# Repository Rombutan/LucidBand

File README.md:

# LucidBand! - The really thin, no-charge smartwatch.
## Philosophy
I quite like the idea of having lots of easily accessible data about myself. Fitness and biological data can be a big help in organizing and optimizing one's life, and I think everyone should have access to that data about *themselves*. 
I want something really thin and somewhat modular that can collect a lot of the data I want to have access to.

## Technology
LucidBand hasa flexible solar cell and everything but the display in the wristband!
The only thing in the face is the display - everything else is on a pcb built into the bottom of the wristband (under your wrist). This lets the face be really thin - hopefully around 7mm - and also allows operation without the display (think: ankle band).
The band will be cast out of a semi-flexible clear epoxy or something.

## Chips
* MCU:			ESP32-C3-WROOM-02-N4
* ENERGY:	  BQ25504
* GYRO:		  BMI270
* SOLAR:		ONP2.4-15X94
<br>
BOM cost for 5 boards with shipping to California turned up to be around 150$. I'm guessing parts for only 1 board would be around 100$ with shipping.

## Screenshots

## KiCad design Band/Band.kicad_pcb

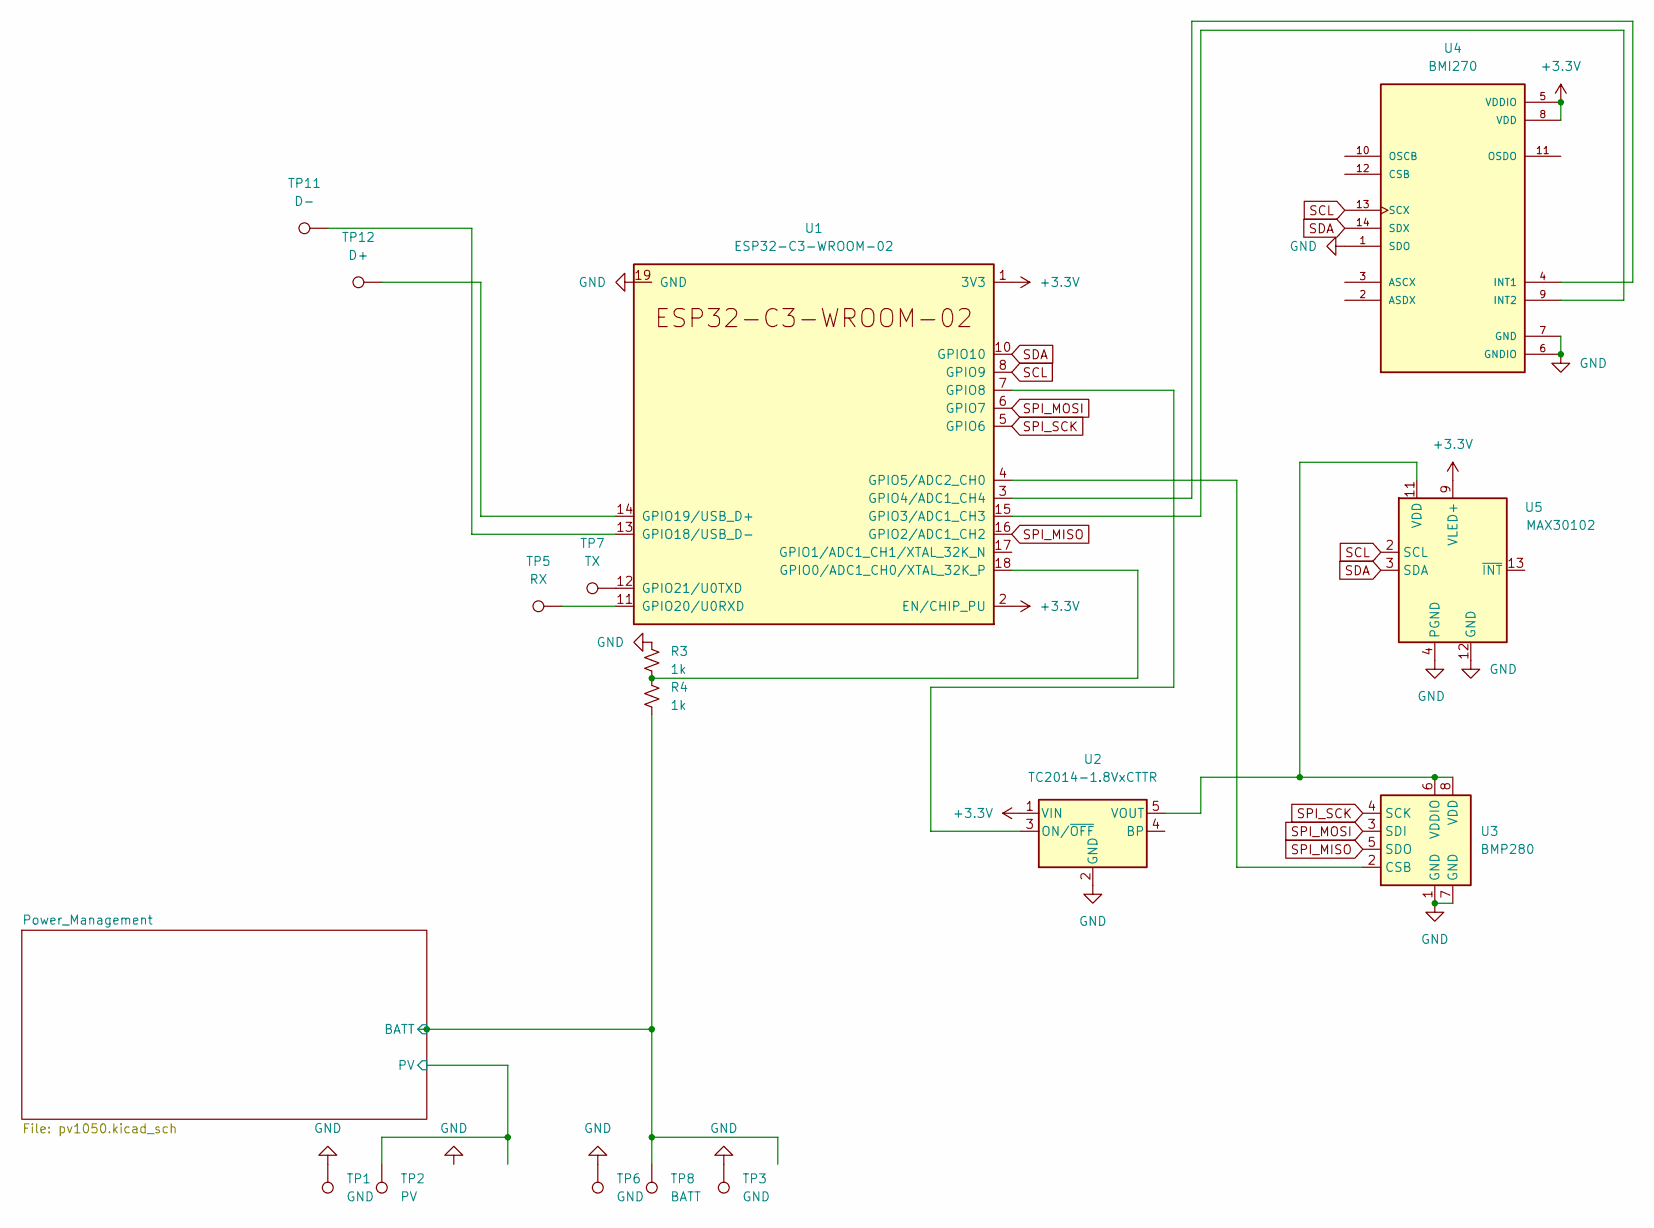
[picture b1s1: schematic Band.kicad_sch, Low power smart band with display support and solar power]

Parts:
R3, R4: 1k; R_0402_1005Metric
TP1, TP3, TP6: GND; TestPoint_Pad_2.0x2.0mm
TP2: PV; TestPoint_Pad_2.0x2.0mm
TP5: RX; TestPoint_Pad_2.0x2.0mm
TP7: TX; TestPoint_Pad_2.0x2.0mm
TP8: BATT; TestPoint_Pad_2.0x2.0mm
TP11: D-; TestPoint_Pad_2.0x2.0mm
TP12: D+; TestPoint_Pad_2.0x2.0mm
U1: ESP32-C3-WROOM-02
U2: TC2014-1.8VxCTTR; SOT-23-5
U3: BMP280; Bosch_LGA-8_2x2.5mm_P0.65mm_ClockwisePinNumbering
U4: BMI270; XDCR_BMI270
U5: MAX30102; Maxim_OLGA-14_3.3x5.6mm_P0.8mm

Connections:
+3.3V: U1.1 (3V3), U1.2 (EN/CHIP_PU), U2.1 (VIN), U4.5 (VDDIO), U4.8 (VDD), U5.9 (VLED+), U5.10 (VLED+); also elsewhere on the board
/Power_Management/BATT: R4.2, TP8.1; also elsewhere on the board
/Power_Management/PV: TP2.1; also elsewhere on the board
GND: R3.1, TP1.1, TP3.1, TP6.1, U1.9 (GND), U1.19 (GND), U2.2 (GND), U3.1 (GND), U3.7 (GND), U4.1 (SDO), U4.6 (GNDIO), U4.7 (GND), U5.4 (PGND), U5.12 (GND); also elsewhere on the board
unnamed: R3.2, R4.1, U1.18 (GPIO0/ADC1_CH0/XTAL_32K_P)
unnamed: TP5.1, U1.11 (GPIO20/U0RXD)
unnamed: TP7.1, U1.12 (GPIO21/U0TXD)
unnamed: U1.3 (GPIO4/ADC1_CH4), U4.4 (INT1)
unnamed: U1.4 (GPIO5/ADC2_CH0), U3.2 (CSB)
unnamed: U1.7 (GPIO8), U2.3 (ON/~OFF)
unnamed: TP11.1, U1.13 (GPIO18/USB_D-)
unnamed: TP12.1, U1.14 (GPIO19/USB_D+)
unnamed: U1.15 (GPIO3/ADC1_CH3), U4.9 (INT2)
unnamed: U2.5 (VOUT), U3.6 (VDDIO), U3.8 (VDD), U5.11 (VDD)
SCL: U1.8 (GPIO9), U4.13 (SCX), U5.2 (SCL)
SDA: U1.10 (GPIO10), U4.14 (SDX), U5.3 (SDA)
SPI_MISO: U1.16 (GPIO2/ADC1_CH2), U3.5 (SDO)
SPI_MOSI: U1.6 (GPIO7), U3.3 (SDI)
SPI_SCK: U1.5 (GPIO6), U3.4 (SCK)

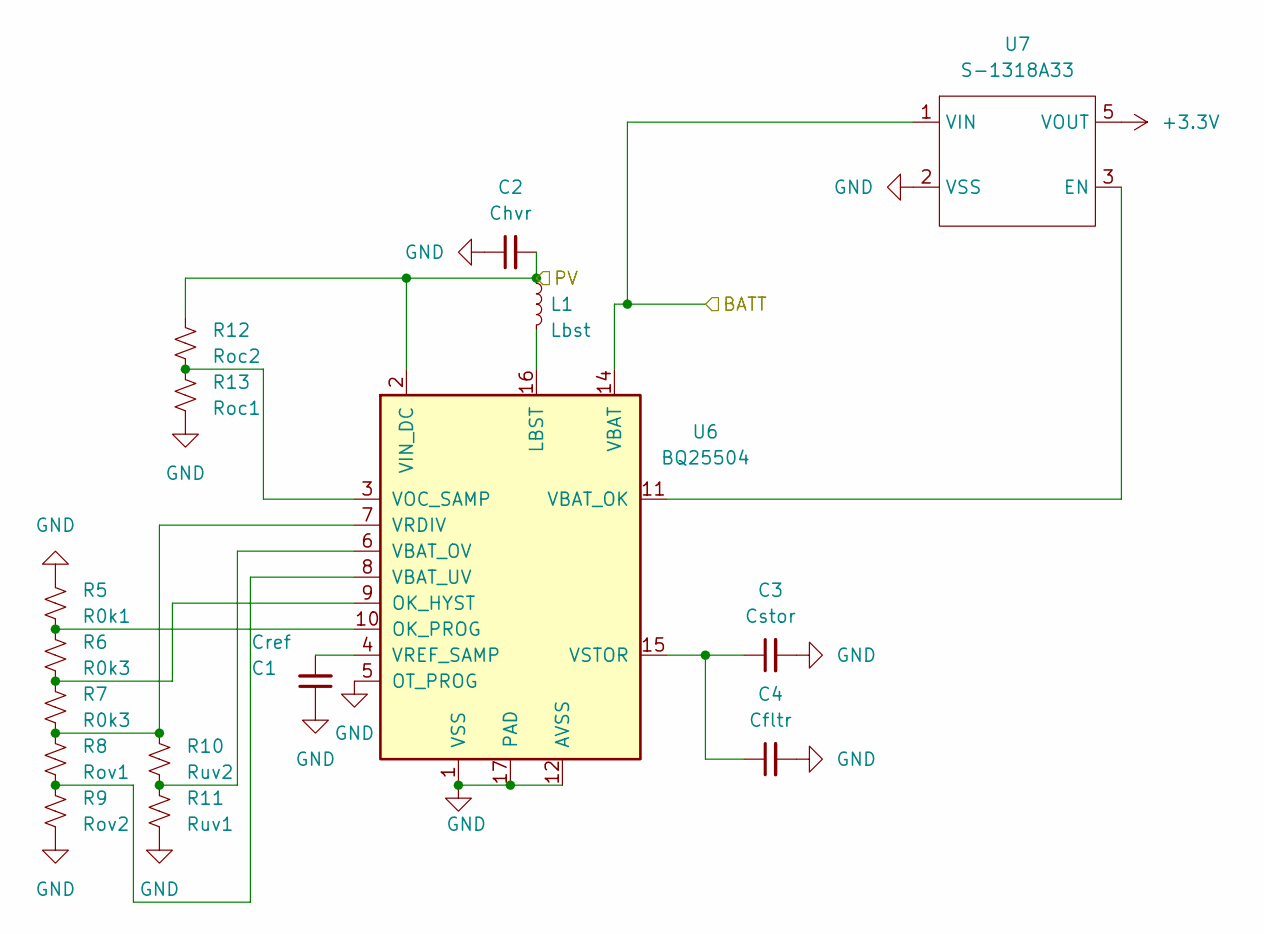
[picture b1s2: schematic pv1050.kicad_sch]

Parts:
C1: Cref; C_0402_1005Metric
C2: Chvr; C_0402_1005Metric
C3: Cstor; C_0805_2012Metric
C4: Cfltr; C_0402_1005Metric
L1: Lbst; L_1210_3225Metric
R5: R0k1; R_0402_1005Metric
R6, R7: R0k3; R_0402_1005Metric
R8: Rov1; R_0402_1005Metric
R9: Rov2; R_0402_1005Metric
R10: Ruv2; R_0402_1005Metric
R11: Ruv1; R_0402_1005Metric
R12: Roc2; R_0402_1005Metric
R13: Roc1; R_0402_1005Metric
U6: BQ25504; VQFN-16-1EP_3x3mm_P0.5mm_EP1.8x1.8mm
U7: S-1318A33; SOT-23-5

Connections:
+3.3V: U7.5 (VOUT); also elsewhere on the board
/Power_Management/BATT: U6.14 (VBAT), U7.1 (VIN); also elsewhere on the board
/Power_Management/PV: C2.2, L1.1, R12.1, U6.2 (VIN_DC); also elsewhere on the board
GND: C1.1, C2.1, C3.2, C4.2, R5.1, R9.2, R11.2, R13.2, U6.1 (VSS), U6.5 (OT_PROG), U6.12 (AVSS), U6.13 (VSS), U6.17 (PAD), U7.2 (VSS); also elsewhere on the board
unnamed: C1.2, U6.4 (VREF_SAMP)
unnamed: C3.1, C4.1, U6.15 (VSTOR)
unnamed: L1.2, U6.16 (LBST)
unnamed: R5.2, R6.1, U6.10 (OK_PROG)
unnamed: R6.2, R7.1, U6.9 (OK_HYST)
unnamed: R8.2, R9.1, U6.8 (VBAT_UV)
unnamed: R7.2, R8.1, R10.1, U6.7 (VRDIV)
unnamed: R10.2, R11.1, U6.6 (VBAT_OV)
unnamed: R12.2, R13.1, U6.3 (VOC_SAMP)
unnamed: U6.11 (VBAT_OK), U7.3 (EN)

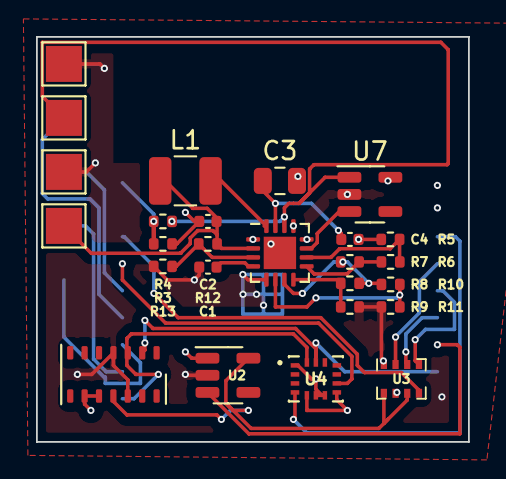
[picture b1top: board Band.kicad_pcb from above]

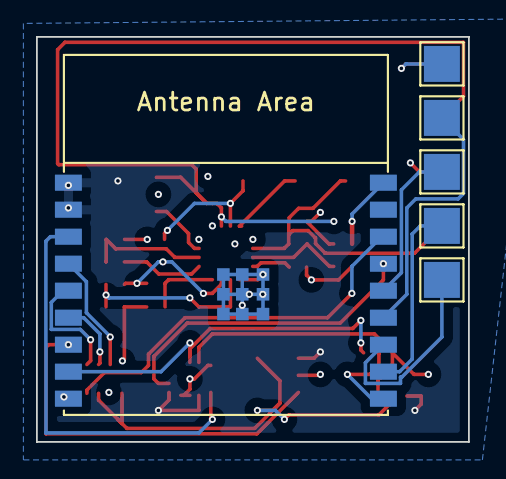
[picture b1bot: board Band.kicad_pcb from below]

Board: 4 copper layers, 24.0 x 22.5 mm, 32 parts (6 on the bottom side), 29 nets.

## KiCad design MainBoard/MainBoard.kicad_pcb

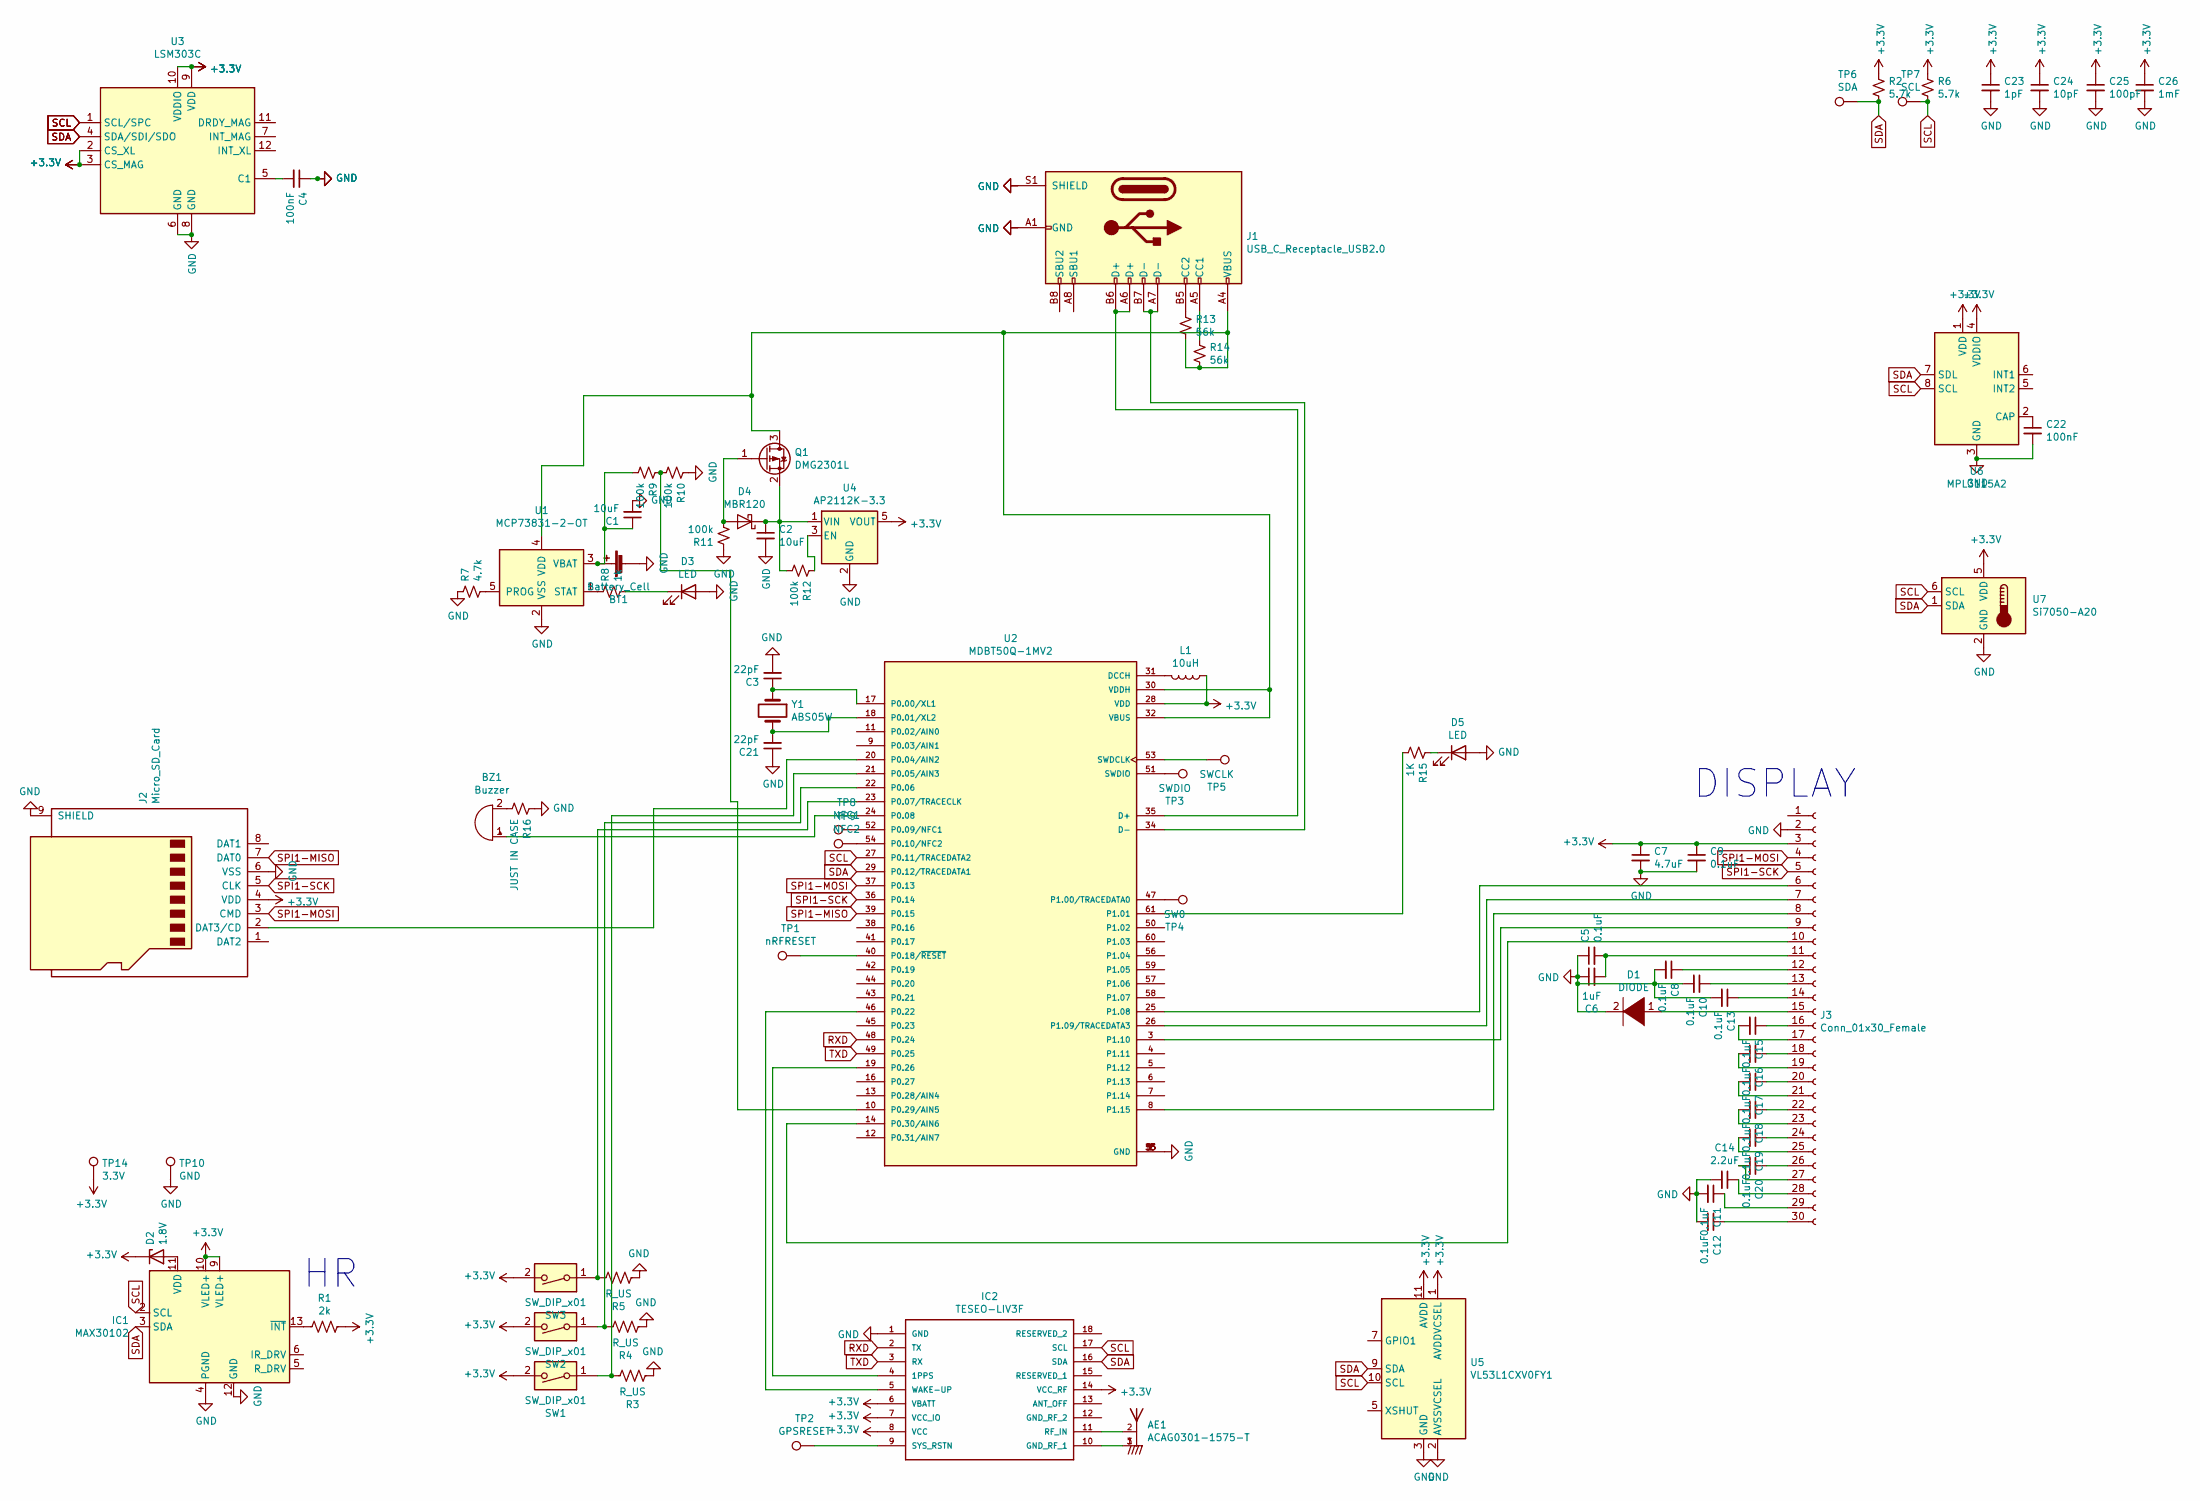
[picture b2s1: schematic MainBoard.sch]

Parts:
AE1: ACAG0301-1575-T; ANT-ACAG0301-1575-T; PARTREV 2018
BT1: Battery_Cell; PinHeader_1x02_P1.27mm_Vertical_SMD_Pin1Left
BZ1: Buzzer; PB9.11-5v
C1, C2: 10uF; C_0402_1005Metric
C3, C21: 22pF; C_0402_1005Metric
C4, C22: 100nF; C_0402_1005Metric
C5, C8, C9, C10, C11, C12, C13, C15, C16, C17, C18, C19, C20: 0.1uF; C_0402_1005Metric
C6: 1uF; C_0402_1005Metric
C7: 4.7uF; C_0402_1005Metric
C14: 2.2uF; C_0402_1005Metric
C23: 1pF; C_0402_1005Metric
C24: 10pF; C_0402_1005Metric
C25: 100pF; C_0402_1005Metric
C26: 1mF; C_0402_1005Metric
D1: DIODE; D_0402_1005Metric
D2: 1.8V; D_SOD-523
D3: LED; LED_0402_1005Metric
D4: MBR120; D_SOD-123F
D5: LED; LED_Kingbright_APFA3010_3x1.5mm_Horizontal
IC1: MAX30102; Maxim_OLGA-14_3.3x5.6mm_P0.8mm
IC2: TESEO-LIV3F; SON110P970X1010X230-18N; MOUSER_PART_NUMBER 511-TESEO-LIV3F
J1: USB_C_Receptacle_USB2.0; USB_C_Receptacle_GCT_USB4085
J2: Micro_SD_Card; microSD_HC_Molex_104031-0811
J3: Conn_01x30_Female; waveshare_1.02
L1: 10uH; L_0402_1005Metric
Q1: DMG2301L; SOT-23
R1: 2k; R_0402_1005Metric
R2, R6: 5.7k; R_0402_1005Metric
R3, R4, R5: R_US; R_0402_1005Metric
R7: 4.7k; R_0402_1005Metric
R8: 1k; R_0402_1005Metric
R9, R10, R11, R12: 100k; R_0402_1005Metric
R13, R14: 56k; R_0402_1005Metric
R15: 1K; R_0402_1005Metric
R16: JUST IN CASE; R_0402_1005Metric
SW1, SW2, SW3: SW_DIP_x01; SW_Push_1P1T-SH_NO_CK_KMR2xxG
TP1: nRFRESET; TestPoint_Pad_2.0x2.0mm
TP2: GPSRESET; TestPoint_Pad_2.0x2.0mm
TP3: SWDIO; TestPoint_Pad_2.0x2.0mm
TP4: SW0; TestPoint_Pad_2.0x2.0mm
TP5: SWCLK; TestPoint_Pad_2.0x2.0mm
TP6: SDA; TestPoint_Pad_2.0x2.0mm
TP7: SCL; TestPoint_Pad_2.0x2.0mm
TP8: NFC1; TestPoint_Pad_2.0x2.0mm
TP9: NFC2; TestPoint_Pad_2.0x2.0mm
TP10: GND; TestPoint_Pad_2.0x2.0mm
TP14: 3.3V; TestPoint_Pad_2.0x2.0mm
U1: MCP73831-2-OT; SOT-23-5
U2: MDBT50Q-1MV2; XCVR_MDBT50Q-1MV2; PARTREV H
U3: LSM303C; LGA-12_2x2mm_P0.5mm
U4: AP2112K-3.3; SOT-23-5
U5: VL53L1CXV0FY1; ST_VL53L1x
U6: MPL3115A2; NXP_LGA-8_3x5mm_P1.25mm_H1.1mm
U7: Si7050-A20; DFN-6-1EP_3x3mm_P1mm_EP1.5x2.4mm
Y1: ABS05W; Crystal_SMD_MicroCrystal_CM9V-T1A-2Pin_1.6x1.0mm

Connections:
+3V3: C7.1, C9.1, C23.1, C24.1, C25.1, C26.1, D2.1 (K), IC1.9 (VLED+), IC1.10 (VLED+), IC2.6 (VBATT), IC2.7 (VCC_IO), IC2.8 (VCC), IC2.14 (VCC_RF), J2.4 (VDD), J3.3, L1.1, R1.1, R2.1, R6.1, SW1.2, SW2.2, SW3.2, TP14.1, U2.28 (VDD), U3.2 (CS_XL), U3.3 (CS_MAG), U3.9 (VDD), U3.10 (VDDIO), U4.5 (VOUT), U5.1 (AVDDVCSEL), U5.11 (AVDD), U6.1 (VDD), U6.4 (VDDIO), U7.5 (VDD)
GND: BT1.2 (-), C1.2, C2.2, C3.2, C4.1, C5.1, C6.1, C7.2, C8.2, C9.2, C10.2, C11.2, C12.2, C13.2, C14.2, C21.1, C22.2, C23.2, C24.2, C25.2, C26.2, D1.2 (A), D3.2 (A), D5.2 (A), IC1.4 (PGND), IC1.12 (GND), IC2.1 (GND), J1.A1 (GND), J1.A12 (GND), J1.B1 (GND), J1.B12 (GND), J1.S1 (SHIELD), J2.6 (VSS), J2.9 (SHIELD), J3.2, R3.2, R4.2, R5.2, R7.1, R10.1, R11.1, R16.1, TP10.1, U1.2 (VSS), U2.1 (GND), U2.2 (GND), U2.15 (GND), U2.33 (GND), U2.55 (GND), U3.6 (GND), U3.8 (GND), U4.2 (GND), U5.2 (AVSSVCSEL), U5.3 (GND), U5.4 (GND), U5.6 (GND), U5.12 (GND), U6.3 (GND), U7.2 (GND)
unnamed: AE1.1, AE1.3, IC2.10 (GND_RF_1)
unnamed: AE1.2, IC2.11 (RF_IN)
unnamed: BT1.1 (+), C1.1, R9.2, U1.3 (VBAT)
unnamed: BZ1.1 (-), U2.24 (P0.08)
unnamed: BZ1.2 (+), R16.2
unnamed: C2.1, D4.1 (K), Q1.2 (S), R12.2, U4.1 (VIN)
unnamed: C3.1, U2.17 (P0.00/XL1), Y1.1
unnamed: C4.2, U3.5 (C1)
unnamed: C5.2, C6.2, J3.11
unnamed: C8.1, J3.12
unnamed: C10.1, J3.13
unnamed: C11.1, J3.29
unnamed: C12.1, J3.30
unnamed: C13.1, J3.14
unnamed: C14.1, J3.28
unnamed: C15.1, J3.16
unnamed: C15.2, J3.17
unnamed: C16.1, J3.18
unnamed: C16.2, J3.19
unnamed: C17.1, J3.20
unnamed: C17.2, J3.21
unnamed: C18.1, J3.22
unnamed: C18.2, J3.23
unnamed: C19.1, J3.24
unnamed: C19.2, J3.25
unnamed: C20.1, J3.26
unnamed: C20.2, J3.27
unnamed: C21.2, U2.18 (P0.01/XL2), Y1.2
unnamed: C22.1, U6.2 (CAP)
unnamed: D1.1 (K), J3.15
unnamed: D2.2 (A), IC1.11 (VDD)
unnamed: D3.1 (K), R8.2
unnamed: D4.2 (A), Q1.1 (G), R11.2
unnamed: D5.1 (K), R15.1
unnamed: IC1.13 (~INT), R1.2
unnamed: IC2.4 (1PPS), U2.19 (P0.26)
unnamed: IC2.5 (WAKE-UP), U2.46 (P0.22)
unnamed: IC2.9 (SYS_RSTN), TP2.1
unnamed: J1.A4 (VBUS), J1.A9 (VBUS), J1.B4 (VBUS), J1.B9 (VBUS), Q1.3 (D), R13.2, R14.2, U1.4 (VDD), U2.30 (VDDH), U2.32 (VBUS)
unnamed: J1.A5 (CC1), R14.1
unnamed: J1.A6 (D+), J1.B6 (D+), U2.35 (D+)
unnamed: J1.A7 (D-), J1.B7 (D-), U2.34 (D-)
unnamed: J1.B5 (CC2), R13.1
unnamed: J2.2 (DAT3/CD), U2.20 (P0.04/AIN2)
unnamed: J3.6, U2.25 (P1.08)
unnamed: J3.7, U2.26 (P1.09/TRACEDATA3)
unnamed: J3.8, U2.8 (P1.15)
unnamed: J3.9, U2.3 (P1.10)
unnamed: J3.10, U2.14 (P0.30/AIN6)
unnamed: L1.2, U2.31 (DCCH)
unnamed: R3.1, SW1.1, U2.21 (P0.05/AIN3)
unnamed: R4.1, SW2.1, U2.22 (P0.06)
unnamed: R5.1, SW3.1, U2.23 (P0.07/TRACECLK)
unnamed: R7.2, U1.5 (PROG)
unnamed: R8.1, U1.1 (STAT)
unnamed: R9.1, R10.2, U2.10 (P0.29/AIN5)
unnamed: R12.1, U4.3 (EN)
unnamed: R15.2, U2.61 (P1.01)
unnamed: TP1.1, U2.40 (P0.18/~RESET)
unnamed: TP3.1, U2.51 (SWDIO)
unnamed: TP4.1, U2.47 (P1.00/TRACEDATA0)
unnamed: TP5.1, U2.53 (SWDCLK)
unnamed: TP8.1, U2.52 (P0.09/NFC1)
unnamed: TP9.1, U2.54 (P0.10/NFC2)
RXD: IC2.2 (TX), U2.48 (P0.24)
SCL: IC1.2 (SCL), IC2.17 (SCL), R6.2, TP7.1, U2.27 (P0.11/TRACEDATA2), U3.1 (SCL/SPC), U5.10 (SCL), U6.8 (SCL), U7.6 (SCL)
SDA: IC1.3 (SDA), IC2.16 (SDA), R2.2, TP6.1, U2.29 (P0.12/TRACEDATA1), U3.4 (SDA/SDI/SDO), U5.9 (SDA), U6.7 (SDL), U7.1 (SDA)
SPI1-MISO: J2.7 (DAT0), U2.39 (P0.15)
SPI1-MOSI: J2.3 (CMD), J3.4, U2.37 (P0.13)
SPI1-SCK: J2.5 (CLK), J3.5, U2.36 (P0.14)
TXD: IC2.3 (RX), U2.49 (P0.25)

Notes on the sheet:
DISPLAY

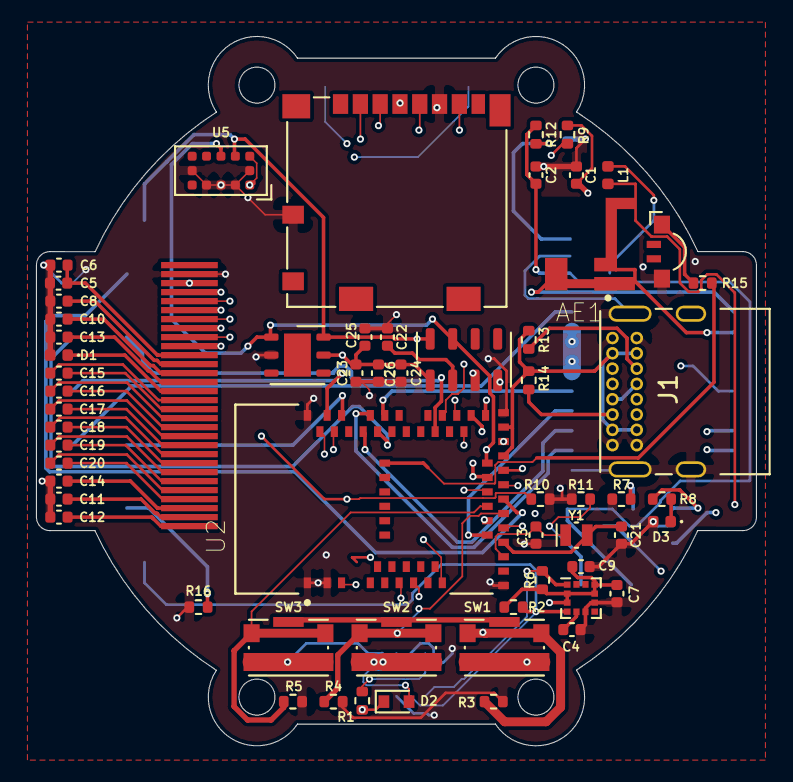
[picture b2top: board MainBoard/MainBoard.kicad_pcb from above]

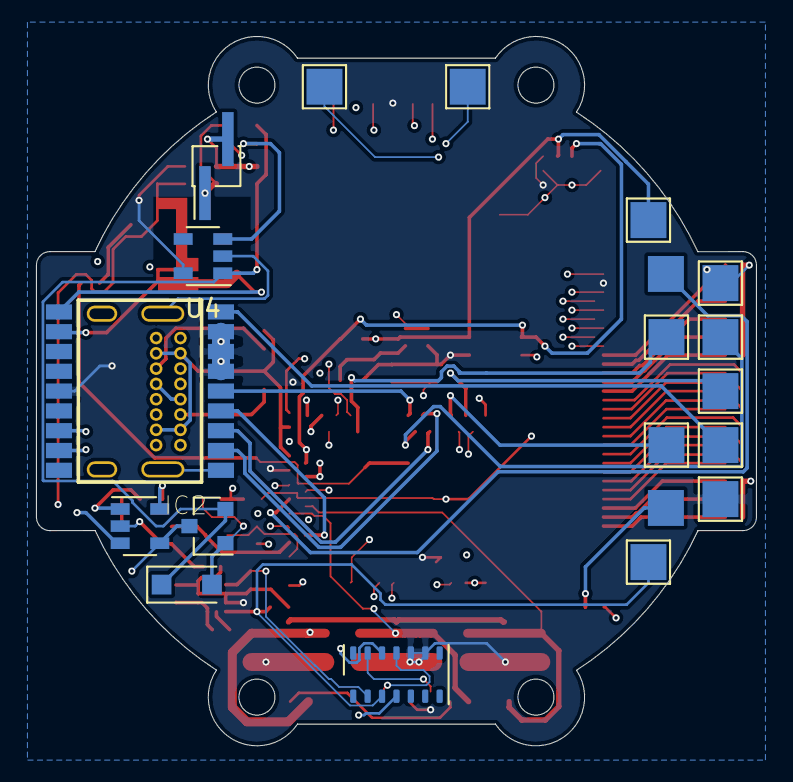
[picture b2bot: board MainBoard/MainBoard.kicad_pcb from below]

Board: 4 copper layers, 40.0 x 39.4 mm, 79 parts (19 on the bottom side), 73 nets.

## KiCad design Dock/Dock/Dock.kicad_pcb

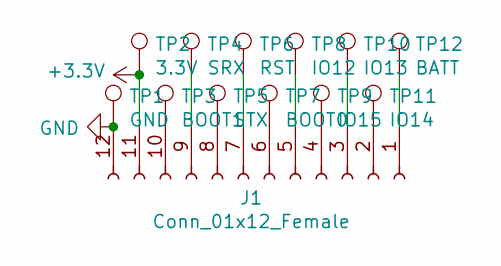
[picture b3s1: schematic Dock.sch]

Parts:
J1: Conn_01x12_Female; PinHeader_1x12_P2.54mm_Horizontal
TP1: GND; 1.01mm
TP2: 3.3V; 1.01mm
TP3: BOOT1; 1.01mm
TP4: SRX; 1.01mm
TP5: STX; 1.01mm
TP6: RST; 1.01mm
TP7: BOOT0; 1.01mm
TP8: IO12; 1.01mm
TP9: IO15; 1.01mm
TP10: IO13; 1.01mm
TP11: IO14; 1.01mm
TP12: BATT; 1.01mm

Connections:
+3V3: J1.11, TP2.1
GND: J1.12, TP1.1
unnamed: J1.1, TP12.1
unnamed: J1.2, TP11.1
unnamed: J1.3, TP10.1
unnamed: J1.4, TP9.1
unnamed: J1.5, TP8.1
unnamed: J1.6, TP7.1
unnamed: J1.7, TP6.1
unnamed: J1.8, TP5.1
unnamed: J1.9, TP4.1
unnamed: J1.10, TP3.1

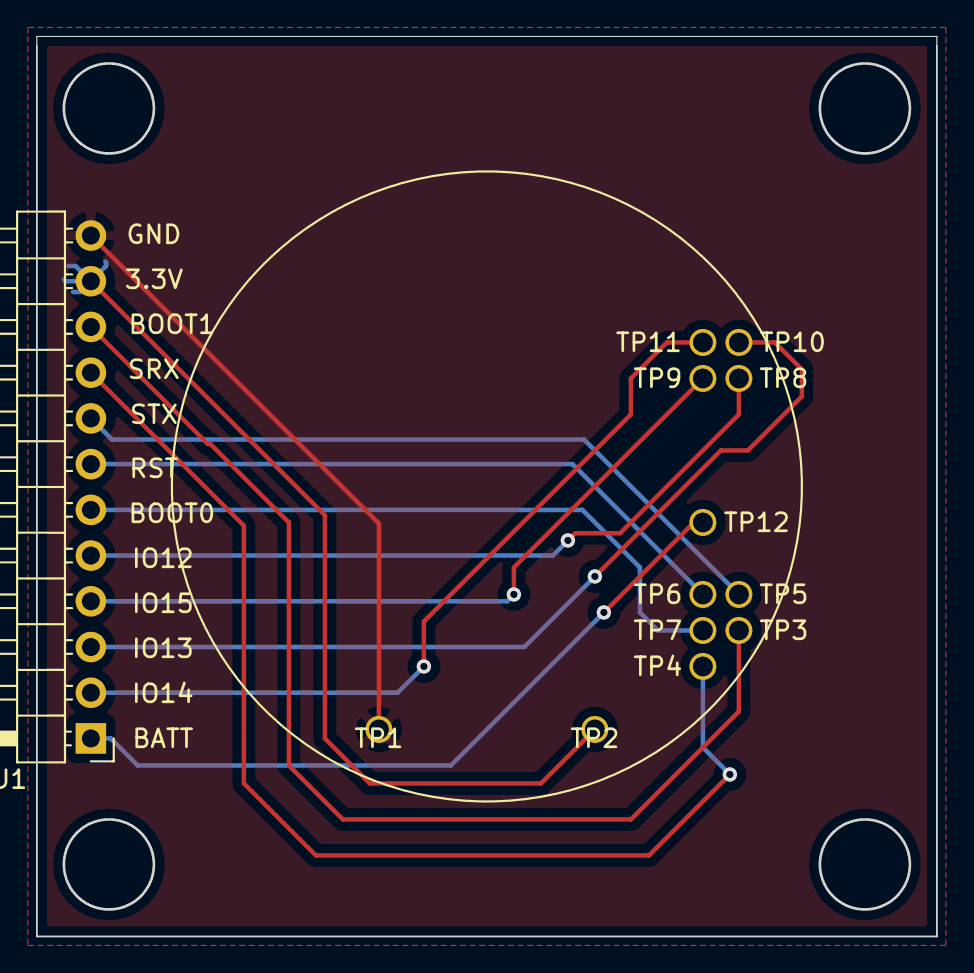
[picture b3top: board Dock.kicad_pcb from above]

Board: 2 copper layers, 49.9 x 49.9 mm, 13 parts (0 on the bottom side), 12 nets.

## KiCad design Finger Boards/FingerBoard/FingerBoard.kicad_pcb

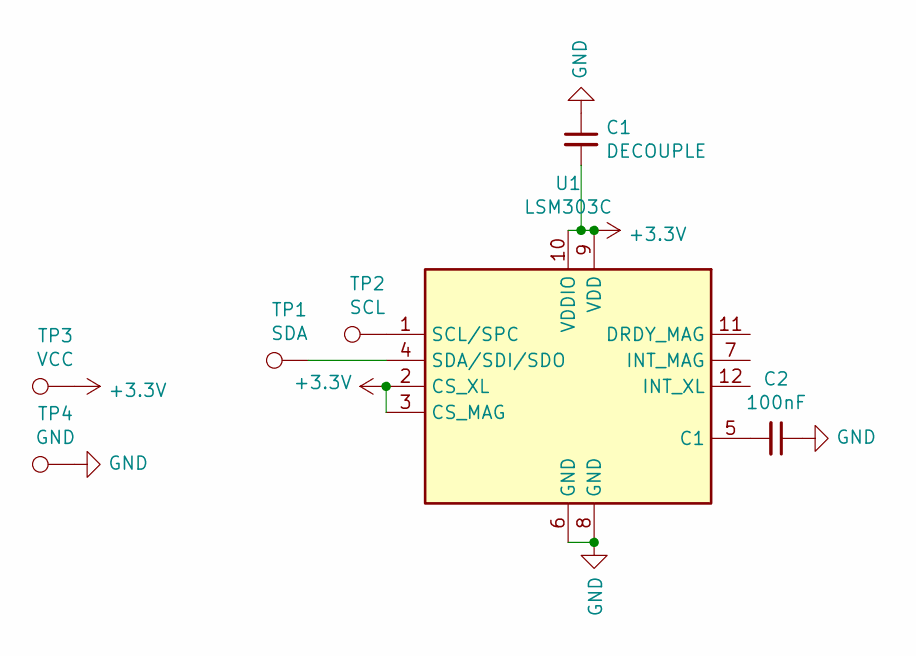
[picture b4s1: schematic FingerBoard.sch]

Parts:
C1: DECOUPLE; C_0402_1005Metric
C2: 100nF; C_0402_1005Metric
TP1: SDA; TestPoint_Pad_1.0x1.0mm
TP2: SCL; TestPoint_Pad_1.0x1.0mm
TP3: VCC; TestPoint_Pad_1.0x1.0mm
TP4: GND; TestPoint_Pad_1.0x1.0mm
U1: LSM303C; LGA-12_2x2mm_P0.5mm

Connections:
+3V3: C1.2, TP3.1, U1.2 (CS_XL), U1.3 (CS_MAG), U1.9 (VDD), U1.10 (VDDIO)
GND: C1.1, C2.1, TP4.1, U1.6 (GND), U1.8 (GND)
unnamed: C2.2, U1.5 (C1)
unnamed: TP1.1, U1.4 (SDA/SDI/SDO)
unnamed: TP2.1, U1.1 (SCL/SPC)

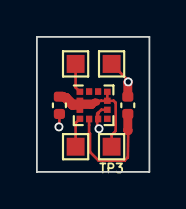
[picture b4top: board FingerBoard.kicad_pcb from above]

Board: 2 copper layers, 6.2 x 7.5 mm, 7 parts (0 on the bottom side), 5 nets.

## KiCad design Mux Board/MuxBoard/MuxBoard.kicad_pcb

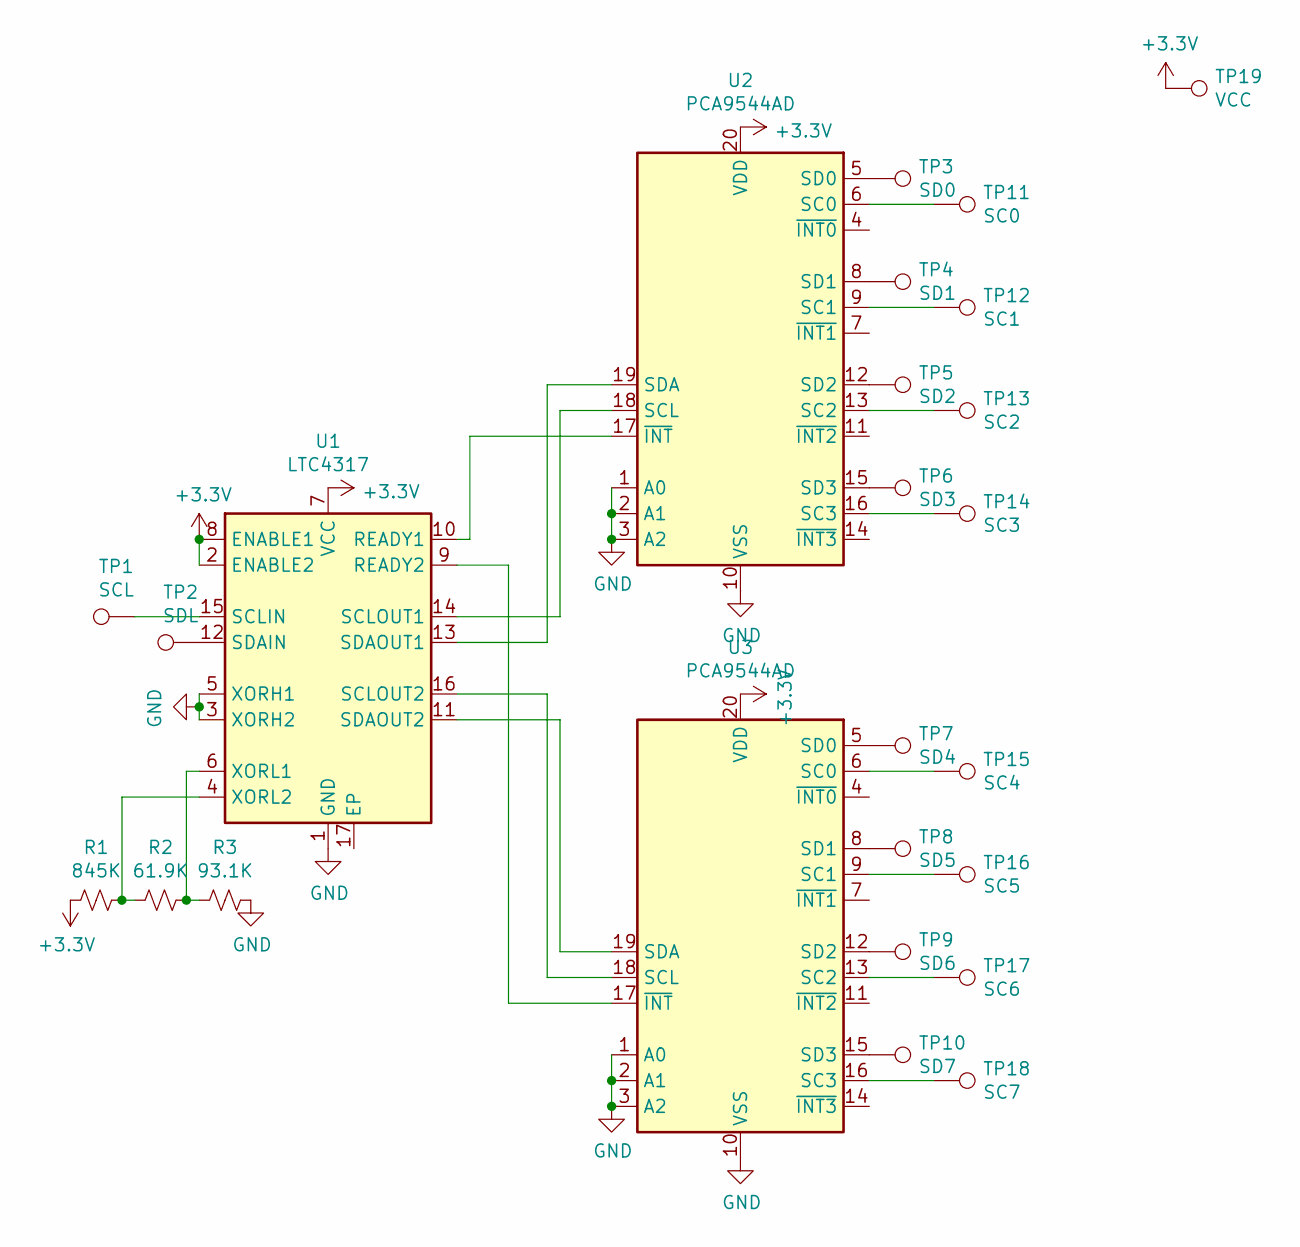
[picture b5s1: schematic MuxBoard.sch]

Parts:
R1: 845K; R_0402_1005Metric
R2: 61.9K; R_0402_1005Metric
R3: 93.1K; TestPoint_Pad_2.0x2.0mm
TP1: SCL; TestPoint_Pad_2.0x2.0mm
TP2: SDL; TestPoint_Pad_2.0x2.0mm
TP3: SD0; TestPoint_Pad_2.0x2.0mm
TP4: SD1; TestPoint_Pad_2.0x2.0mm
TP5: SD2; TestPoint_Pad_2.0x2.0mm
TP6: SD3; TestPoint_Pad_2.0x2.0mm
TP7: SD4; TestPoint_Pad_2.0x2.0mm
TP8: SD5; TestPoint_Pad_2.0x2.0mm
TP9: SD6; TestPoint_Pad_2.0x2.0mm
TP10: SD7; TestPoint_Pad_2.0x2.0mm
TP11: SC0; TestPoint_Pad_2.0x2.0mm
TP12: SC1; TestPoint_Pad_2.0x2.0mm
TP13: SC2; TestPoint_Pad_2.0x2.0mm
TP14: SC3; TestPoint_Pad_2.0x2.0mm
TP15: SC4; TestPoint_Pad_2.0x2.0mm
TP16: SC5; TestPoint_Pad_2.0x2.0mm
TP17: SC6; TestPoint_Pad_2.0x2.0mm
TP18: SC7; TestPoint_Pad_2.0x2.0mm
TP19: VCC; TestPoint_Pad_2.0x2.0mm
U1: LTC4317; DFN-16-1EP_3x5mm_P0.5mm_EP1.66x4.4mm
U2, U3: PCA9544AD; SOIC-20W_7.5x12.8mm_P1.27mm

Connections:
+3V3: R1.2, TP19.1, U1.2 (ENABLE2), U1.7 (VCC), U1.8 (ENABLE1), U2.20 (VDD), U3.20 (VDD)
GND: R3.1, U1.1 (GND), U1.3 (XORH2), U1.5 (XORH1), U2.1 (A0), U2.2 (A1), U2.3 (A2), U2.10 (VSS), U3.1 (A0), U3.2 (A1), U3.3 (A2), U3.10 (VSS)
unnamed: R1.1, R2.2, U1.4 (XORL2)
unnamed: R2.1, R3.2, U1.6 (XORL1)
unnamed: TP1.1, U1.15 (SCLIN)
unnamed: TP2.1, U1.12 (SDAIN)
unnamed: TP3.1, U2.5 (SD0)
unnamed: TP4.1, U2.8 (SD1)
unnamed: TP5.1, U2.12 (SD2)
unnamed: TP6.1, U2.15 (SD3)
unnamed: TP7.1, U3.5 (SD0)
unnamed: TP8.1, U3.8 (SD1)
unnamed: TP9.1, U3.12 (SD2)
unnamed: TP10.1, U3.15 (SD3)
unnamed: TP11.1, U2.6 (SC0)
unnamed: TP12.1, U2.9 (SC1)
unnamed: TP13.1, U2.13 (SC2)
unnamed: TP14.1, U2.16 (SC3)
unnamed: TP15.1, U3.6 (SC0)
unnamed: TP16.1, U3.9 (SC1)
unnamed: TP17.1, U3.13 (SC2)
unnamed: TP18.1, U3.16 (SC3)
unnamed: U1.9 (READY2), U3.17 (~INT)
unnamed: U1.10 (READY1), U2.17 (~INT)
unnamed: U1.11 (SDAOUT2), U3.19 (SDA)
unnamed: U1.13 (SDAOUT1), U2.19 (SDA)
unnamed: U1.14 (SCLOUT1), U2.18 (SCL)
unnamed: U1.16 (SCLOUT2), U3.18 (SCL)

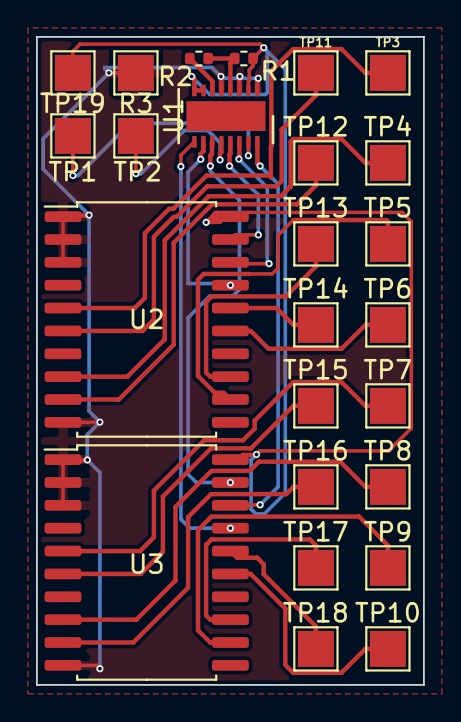
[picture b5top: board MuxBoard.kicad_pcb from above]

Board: 2 copper layers, 21.5 x 36.0 mm, 25 parts (0 on the bottom side), 28 nets.

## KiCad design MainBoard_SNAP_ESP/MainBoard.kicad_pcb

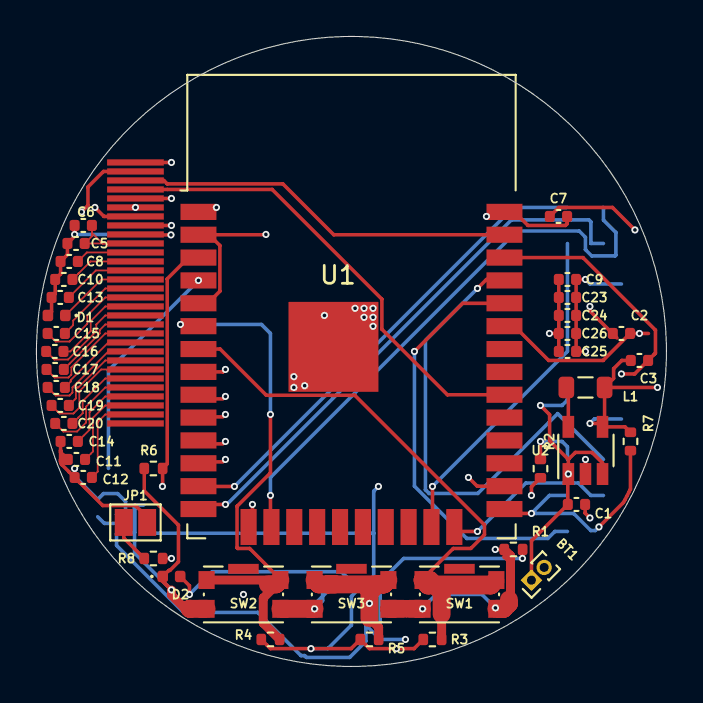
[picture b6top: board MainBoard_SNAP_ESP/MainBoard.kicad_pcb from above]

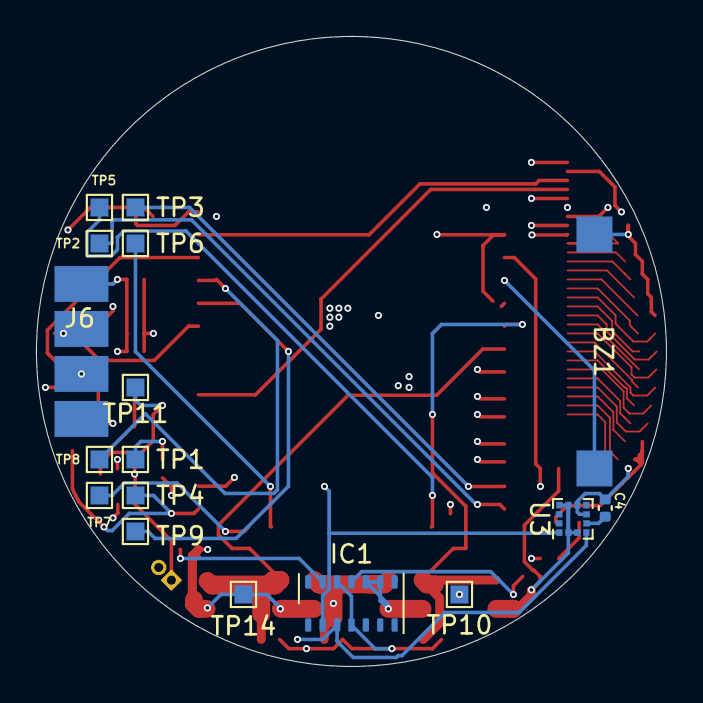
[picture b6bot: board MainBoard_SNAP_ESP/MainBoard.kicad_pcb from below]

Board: 4 copper layers, 35.0 x 35.0 mm, 59 parts (17 on the bottom side), 51 nets.

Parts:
BT1: Battery_Cell; PinHeader_1x02_P1.00mm_Vertical
BZ1: Buzzer; PB9.11-5v
C1: 4.5uF; C_0402_1005Metric
C2, C3: 5.7k; C_0402_1005Metric
C4: 100nF; C_0402_1005Metric
C5, C8, C9, C10, C11, C12, C13, C15, C16, C17, C18, C19, C20: 0.1uF; C_0402_1005Metric
C6: 1uF; C_0402_1005Metric
C7: 4.7uF; C_0402_1005Metric
C14: 2.2uF; C_0402_1005Metric
C23: 1pF; C_0402_1005Metric
C24: 10pF; C_0402_1005Metric
C25: 100pF; C_0402_1005Metric
C26: 1mF; C_0402_1005Metric
D1: DIODE; D_0402_1005Metric
D2: 1.8V; D_0402_1005Metric
IC1: MAX30102; Maxim_OLGA-14_3.3x5.6mm_P0.8mm
J3: Conn_01x30_Female; waveshare_1.02
J6: Conn_01x04; 4 Pin SMD Wire
JP1: WP; SolderJumper-2_P1.3mm_Open_Pad1.0x1.5mm
L1: 1uH; L_0805_2012Metric
R1, R2, R6, R7, R8: 2k; R_0402_1005Metric
R3, R4, R5: R_US; R_0402_1005Metric
SW1, SW2, SW3: SW_DIP_x01; SW_Push_1P1T-SH_NO_CK_KMR2xxG
TP1: RST; TestPoint_Pad_1.0x1.0mm
TP2: IO12; TestPoint_Pad_1.0x1.0mm
TP3: IO14; TestPoint_Pad_1.0x1.0mm
TP4: BOOT0; TestPoint_Pad_1.0x1.0mm
TP5: IO13; TestPoint_Pad_1.0x1.0mm
TP6: IO15; TestPoint_Pad_1.0x1.0mm
TP7: BOOT1; TestPoint_Pad_1.0x1.0mm
TP8: STX; TestPoint_Pad_1.0x1.0mm
TP9: SRX; TestPoint_Pad_1.0x1.0mm
TP10: GND; TestPoint_Pad_1.0x1.0mm
TP11: BATT; TestPoint_Pad_1.0x1.0mm
TP14: 3.3V; TestPoint_Pad_1.0x1.0mm
U1: ESP32-WROOM-32
U2: ADP2108AUJ-3.3; TSOT-23-5
U3: LSM303C; LGA-12_2x2mm_P0.5mm

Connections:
+3V3: C2.1, C3.1, C7.1, C9.1, C23.1, C24.1, C25.1, C26.1, D2.1, IC1.9, IC1.10, J3.2, J6.1, L1.2, R1.1, R6.1, R7.2, SW1.2, SW2.2, SW3.2, TP14.1, U1.2, U1.5, U2.4, U3.2, U3.3, U3.9, U3.10
GND: BT1.2, BZ1.1, C1.2, C4.1, C5.1, C6.1, C7.2, C8.2, C9.2, C10.2, C11.2, C12.2, C13.2, C14.2, C23.2, C24.2, C25.2, C26.2, D1.2, IC1.4, IC1.12, J3.1, J6.4, JP1.2, R3.2, R4.2, R5.2, TP10.1, U1.1, U1.15, U1.38, U1.39, U2.2, U3.6, U3.8
unnamed: BT1.1, C1.1, TP11.1, U2.1, U2.3
unnamed: BZ1.2, U1.4
unnamed: C4.2, U3.5
unnamed: C5.2, C6.2, J3.10
unnamed: C8.1, J3.11
unnamed: C10.1, J3.12
unnamed: C11.1, J3.28
unnamed: C12.1, J3.29
unnamed: C13.1, J3.13
unnamed: C14.1, J3.27
unnamed: C15.1, J3.15
unnamed: C15.2, J3.16
unnamed: C16.1, J3.17
unnamed: C16.2, J3.18
unnamed: C17.1, J3.19
unnamed: C17.2, J3.20
unnamed: C18.1, J3.21
unnamed: C18.2, J3.22
unnamed: C19.1, J3.23
unnamed: C19.2, J3.24
unnamed: C20.1, J3.25
unnamed: C20.2, J3.26
unnamed: D1.1, J3.14
unnamed: D2.2, IC1.11
unnamed: IC1.13, R1.2
unnamed: J3.5, U1.10
unnamed: J3.6, U1.11
unnamed: J3.7, U1.12
unnamed: J3.8, U1.8
unnamed: J3.9, U1.9
unnamed: JP1.1, R8.1
unnamed: L1.1, U2.5
unnamed: R2.1, R6.2, U1.3
unnamed: R2.2, TP1.1
unnamed: R3.1, SW1.1, U1.7
unnamed: R4.1, SW2.1, U1.6
unnamed: R5.1, SW3.1, U1.26
unnamed: R7.1, TP4.1, U1.25
unnamed: R8.2, TP7.1, U1.24
unnamed: TP2.1, U1.14
unnamed: TP3.1, U1.13
unnamed: TP5.1, U1.16
unnamed: TP6.1, U1.23
unnamed: TP8.1, U1.35
unnamed: TP9.1, U1.34
SCL: C3.2, IC1.2, J6.2, U1.36, U3.1
SDA: C2.2, IC1.3, J6.3, U1.33, U3.4
SPI1-MOSI: J3.3, U1.37
SPI1-SCK: J3.4, U1.30

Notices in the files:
parts and their libraries:
Copyright 2016 Accelerated Designs. All rights reserved.
